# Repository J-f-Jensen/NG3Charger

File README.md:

# NG3Charger
Zivan NG3 charger diy control board, developed in arduino's C/C++

Required CAN library can be found here: 
https://github.com/coryjfowler/MCP_CAN_lib

When code is compiled and uploaded you can connect via serial terminal at 9600baud rate. 

Send ? to get help menu

Its possible to calibrate voltage by following the guide when you send an uppercase S

Remember to save configuration by seending uppercase S followed by lowercase s

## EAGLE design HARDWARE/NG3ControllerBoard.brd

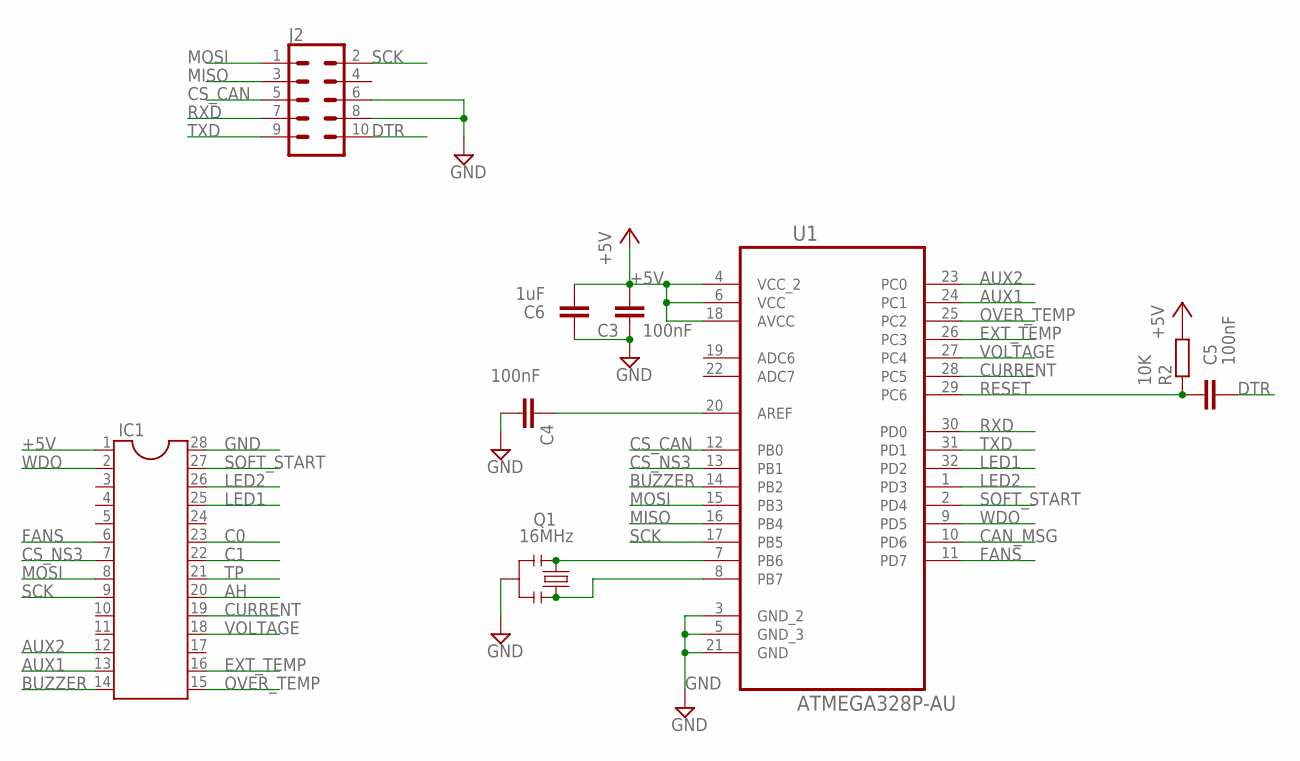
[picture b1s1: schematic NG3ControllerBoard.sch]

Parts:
C3, C4, C5: 100nF; C0603
C6: 1uF; C0805
IC1: DIL28; DIL28-6
J2: CONN_05X2PTH; 2X5
Q1: 16MHz; RESONATOR-SMD
R2: 10K; R0603
U1: ATMEGA328P-AU; QFP80P900X900X120-32N

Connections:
+5V: C3.2, C6.2, IC1.1, R2.2, U1.4 (VCC_2), U1.6 (VCC), U1.18 (AVCC)
AH: IC1.20
AUX1: IC1.13, U1.24 (PC1)
AUX2: IC1.12, U1.23 (PC0)
BUZZER: IC1.14, U1.14 (PB2)
C0: IC1.23
C1: IC1.22
CAN_MSG: U1.10 (PD6)
CS_CAN: J2.5, U1.12 (PB0)
CS_NS3: IC1.7, U1.13 (PB1)
CURRENT: IC1.19, U1.28 (PC5)
DTR: C5.2, J2.10
EXT_TEMP: IC1.16, U1.26 (PC3)
FANS: IC1.6, U1.11 (PD7)
GND: C3.1, C4.2, C6.1, IC1.28, J2.6, J2.8, Q1.2, U1.3 (GND_2), U1.5 (GND_3), U1.21 (GND)
LED1: IC1.25, U1.32 (PD2)
LED2: IC1.26, U1.1 (PD3)
MISO: J2.3, U1.16 (PB4)
MOSI: IC1.8, J2.1, U1.15 (PB3)
unnamed: Q1.1, U1.7 (PB6)
unnamed: Q1.3, U1.8 (PB7)
unnamed: C4.1, U1.20 (AREF)
OVER_TEMP: IC1.15, U1.25 (PC2)
RESET: C5.1, R2.1, U1.29 (PC6)
RXD: J2.7, U1.30 (PD0)
SCK: IC1.9, J2.2, U1.17 (PB5)
SOFT_START: IC1.27, U1.2 (PD4)
TP: IC1.21
TXD: J2.9, U1.31 (PD1)
VOLTAGE: IC1.18, U1.27 (PC4)
WDO: IC1.2, U1.9 (PD5)

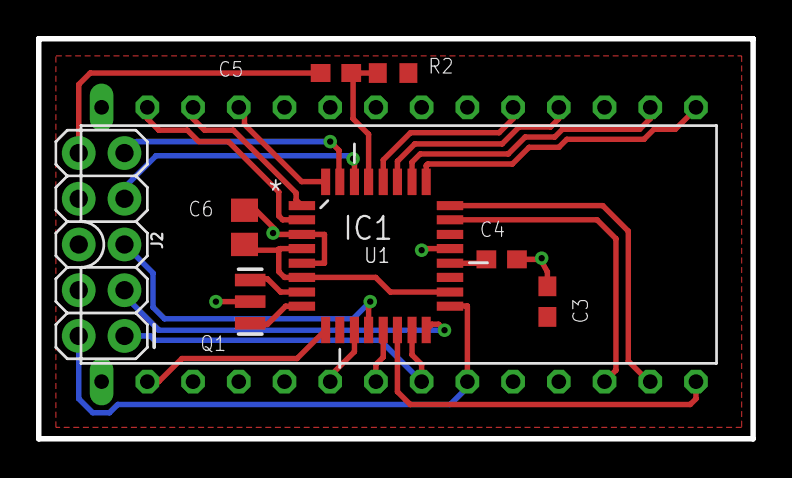
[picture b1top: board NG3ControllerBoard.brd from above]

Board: 2 copper layers, 39.7 x 22.2 mm, 9 parts (0 on the bottom side), 26 nets.

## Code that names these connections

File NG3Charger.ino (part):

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// These define the digital output pins used to control various
// features of the board.
#define CS_NG3_PIN          9  //Chip select for the digital potentiometer
#define CS_CAN_PIN          8  //Chip select for the MCP2515 CAN controller
#define CAN_MSG_PIN         6  //Input pin used to check if MCP2515 CAN controller have recived a message
#define SOFT_START_PIN      4  //Soft start pin, used to enable/disable charging
#define WDO_PIN             5  //Watchdog Output pin, must toggle to keep charger running
#define FANS_PIN            7  //Enables the fans
#define AUX1_PIN            15 //Controls aux relay #1
#define AUX2_PIN            14 //Controls aud relay #2
#define BUZZER_PIN          10 //Controls digital sounder, requires a square wave for sound
#define LEDG_PIN            2  //Controls the green LED (LED1)
#define LEDR_PIN            3  //Controls the red LED (LED2)
// SS                  10 // Slave select is used for the BUZZER
// MOSI                11
// MISO                12
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#define AD_CURRENT     A5

// Declare CAN module
MCP_CAN CAN0(CS_CAN_PIN);

// Declare serial communication 
SERIALCOMM SerialCom;
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unsigned char  digital_pot_max_bits = 0;
unsigned char  calibrationStatus = 0;

float over_temp = 0;
float ext_temp = 0;
unsigned short voltage = 0;
unsigned short current = 0;
 
#define IDLE_STATE             0
#define SOFT_START       1
#define CONSTANT_CURRENT 2
#define CONSTANT_VOLTAGE 3
#define TEST_MODE        4
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  pinMode(MOSI,OUTPUT);  // This should be default when loading the SPI module
  pinMode(SS,OUTPUT);    // This should be default when loading the SPI module
  pinMode(CS_NG3_PIN,OUTPUT);
  pinMode(CS_CAN_PIN,OUTPUT);
  pinMode(SOFT_START_PIN,OUTPUT);
  pinMode(WDO_PIN,OUTPUT);
  pinMode(FANS_PIN,OUTPUT);
  pinMode(AUX1_PIN,OUTPUT);
  pinMode(AUX2_PIN,OUTPUT);
  pinMode(BUZZER_PIN,OUTPUT);
  pinMode(LEDG_PIN,OUTPUT);
  pinMode(LEDR_PIN,OUTPUT);
 
  digitalWrite(SOFT_START_PIN,HIGH);       
  digitalWrite(SS,HIGH);
  digitalWrite(CS_NG3_PIN,HIGH); 
  digitalWrite(CS_CAN_PIN,HIGH);
  digitalWrite(BUZZER_PIN, LOW);

  // Starte Serial
  SerialCom.begin();
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  }
  else
  {
    //Set the constant voltage settings of the AD8402
    digital_pot_bits  = (unsigned char)(((settings.CHARGE_CONSTANT_VOLTAGE + settings.CHARGER_VOLTAGE_OFFSET_POT) - settings.CHARGER_MIN_VOLTS)*100 / (ChargerVoltagePrAD8402Bit) );
    set_cv(digital_pot_bits);
    
    //Set the constant current settings of the AD8402
    digital_pot_bits  = (unsigned char)( settings.CHARGE_CONSTANT_CURRENT*100 / settings.CHARGER_CURRENT_AD8402_mA_PER_BIT );
    set_cc(digital_pot_bits);
    
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  }

  //Sound the buzzer at 2000Hz in 1 sec - just for the heck of it
  tone(BUZZER_PIN, 2000, 1000);

}

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    // Toggle the NG3 watchdog timer, it must be toggled frequently to keep the logic
    // board's reset controller from thinking the microprocessor is locked up and
    // shutting down the output.
    digitalWrite(WDO_PIN,1);
    digitalWrite(WDO_PIN,0);

}/////END OF LOOP

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//Set the connstant voltage setting
void set_cv(unsigned char bits)
{
  //Set the constant voltage settings of the AD8402
  digitalWrite(CS_NG3_PIN, 0);
  SPI.transfer(0x01);
  SPI.transfer(bits);
  digitalWrite(CS_NG3_PIN, 1);
}

//Set the constant current setting
void set_cc(unsigned char bits)
{
  //Set the constant current settings of the AD8402
  digitalWrite(CS_NG3_PIN, 0);
  SPI.transfer(0x00);
  SPI.transfer(bits);
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    // If first time through, go to the CONSTANT_CURRENT state and
    // enable the charger output
    if( state == SOFT_START ) {
       state = CONSTANT_CURRENT; //Now we are in constant current state

       // If SOFT_START_PIN not is enabled e.g. = 0 then enable it
       if (digitalRead(SOFT_START_PIN) == 1)
       {
        digitalWrite(SOFT_START_PIN, 0); // Setting SOFT_START pin to low enables the actual output of the charger
       }
 
       // Set the LED and AUX relays any way you want for the CC state
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       // Both LEDs set to 0 gives the YELLOW color.
        digitalWrite(LEDG_PIN, 1);
        digitalWrite(LEDR_PIN, 0);
        digitalWrite(AUX1_PIN, 0);
        digitalWrite(AUX2_PIN, 1);
  //      digitalWrite(FANS_PIN,1); // Start the fans

     // Currently in the constant current mode
    } else if ( state == CONSTANT_CURRENT ) {

      // stay in constant current mode until the voltage >= CV setpoint then go to CV state
      if( GlobalData.Voltage >= settings.CHARGE_CONSTANT_VOLTAGE ) {
        //Now we are in the constant voltage state
        state = CONSTANT_VOLTAGE; 

        // Set the LED and AUX relays any way you want for the CV state
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        // Both LEDs set to 0 gives the YELLOW color.
        digitalWrite(LEDG_PIN, 0);
        digitalWrite(LEDR_PIN, 0);
        digitalWrite(AUX1_PIN, 1);
        digitalWrite(AUX2_PIN, 1);
      }

    //  Currently in the constant voltage mode
    } else if ( state == CONSTANT_VOLTAGE ) {
  
      //Stay in CV state until current drops to Imin then goto IDLE state
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        // Both LEDs set to 0 gives the YELLOW color.
        digitalWrite(LEDG_PIN, 0);
        digitalWrite(LEDR_PIN, 1);
        digitalWrite(AUX1_PIN, 1);
        digitalWrite(AUX2_PIN, 0);
        digitalWrite(SOFT_START_PIN,1);   // Turns off the chargers output
        digitalWrite(FANS_PIN,0); // Stops the fans
      }
    }
  }
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    // Check if recived values have changed - if not its just a heartbeat message 
    if ( recivedVoltageValue != CAN_VoltageValue )
    {
      //Set the constant voltage settings of the AD8402
      digital_pot_bits  = (unsigned char)(( (recivedVoltageValue + settings.CHARGER_VOLTAGE_OFFSET_POT) - settings.CHARGER_MIN_VOLTS )*100 / ChargerVoltagePrAD8402Bit );
      set_cv(digital_pot_bits);
      
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    if ( recivedCurrentValue != CAN_CurrentValue )
    {
            
      //Set the constant current settings of the AD8402
      digital_pot_bits  = (unsigned char)( recivedCurrentValue * 100 / settings.CHARGER_CURRENT_AD8402_mA_PER_BIT );
      set_cc(digital_pot_bits); 
      
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
    if ( rxBuf[4] == 0 ) // Start charging if 0 - all other values turnoff the charger
    {
      digitalWrite(SOFT_START_PIN,0); 
    }
    else
    {
      CAN_TimeOut = true;
      digitalWrite(SOFT_START_PIN,1); 
    }
  }

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  
  if ( CAN_TimeOut ) // Turn off the chargers output if CAN_TimeOut is true
  { 
    digitalWrite(SOFT_START_PIN,1); 
  }
}

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    digitalWrite(LEDR_PIN, 0);

    // Enable charger output
    digitalWrite(SOFT_START_PIN, LOW);

    for (int i=0;i<127;i++)
    {
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      }

      // Keep the NG3 watchdog happy
      digitalWrite(WDO_PIN,1);
      digitalWrite(WDO_PIN,0);
    }

    // Copy to the "global" values
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      digitalWrite(LEDG_PIN, !digitalRead(LEDG_PIN));

      // Keep the NG3 watchdog happy
      digitalWrite(WDO_PIN,1);
      digitalWrite(WDO_PIN,0);
    }

    // Disable the output from the charger
    digitalWrite(SOFT_START_PIN, HIGH);
}

void ChargerTestMode(void)
{  
  //Set the constant voltage settings of the AD8402
  digital_pot_bits  = (unsigned char)( ((settings.CHARGE_CONSTANT_VOLTAGE + settings.CHARGER_VOLTAGE_OFFSET_POT) - settings.CHARGER_MIN_VOLTS)*100 / (ChargerVoltagePrAD8402Bit) );
  set_cv(digital_pot_bits);
  
  //Set the constant current settings of the AD8402
  digital_pot_bits  = (unsigned char)( settings.CHARGE_CONSTANT_CURRENT*100 / settings.CHARGER_CURRENT_AD8402_mA_PER_BIT );
  set_cc(digital_pot_bits);

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  digitalWrite(LEDR_PIN, 0);

  // Enable charger output
  digitalWrite(SOFT_START_PIN, LOW);

  // Every 500ms tasks
  if (millis() - looptime_1s > 500UL )
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    if (testModeTimer == 120) // End of test mode
    {
      // Disable the output from the charger
      digitalWrite(SOFT_START_PIN, HIGH);
    
      // Switch to idle mode - only relevant in standalon mode
      state = IDLE_STATE;
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
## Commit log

2020-08-06 Documents added

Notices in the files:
parts and their libraries:
SparkFun-Connectors: Licensing: Creative Commons ShareAlike 4.0 International - https://creativecommons.org/licenses/by-sa/4.0
SparkFun: Licensing: CC v3.0 Share-Alike You are welcome to use this library for commercial purposes.
